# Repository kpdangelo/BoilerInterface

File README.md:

# BoilerInterface
This is an Arduino pro-mini 3.3v controlled interface between an old Tekmar controller and a new boiler.  It translates a BTU command from the controller to a Temperature setpoint for the boiler.

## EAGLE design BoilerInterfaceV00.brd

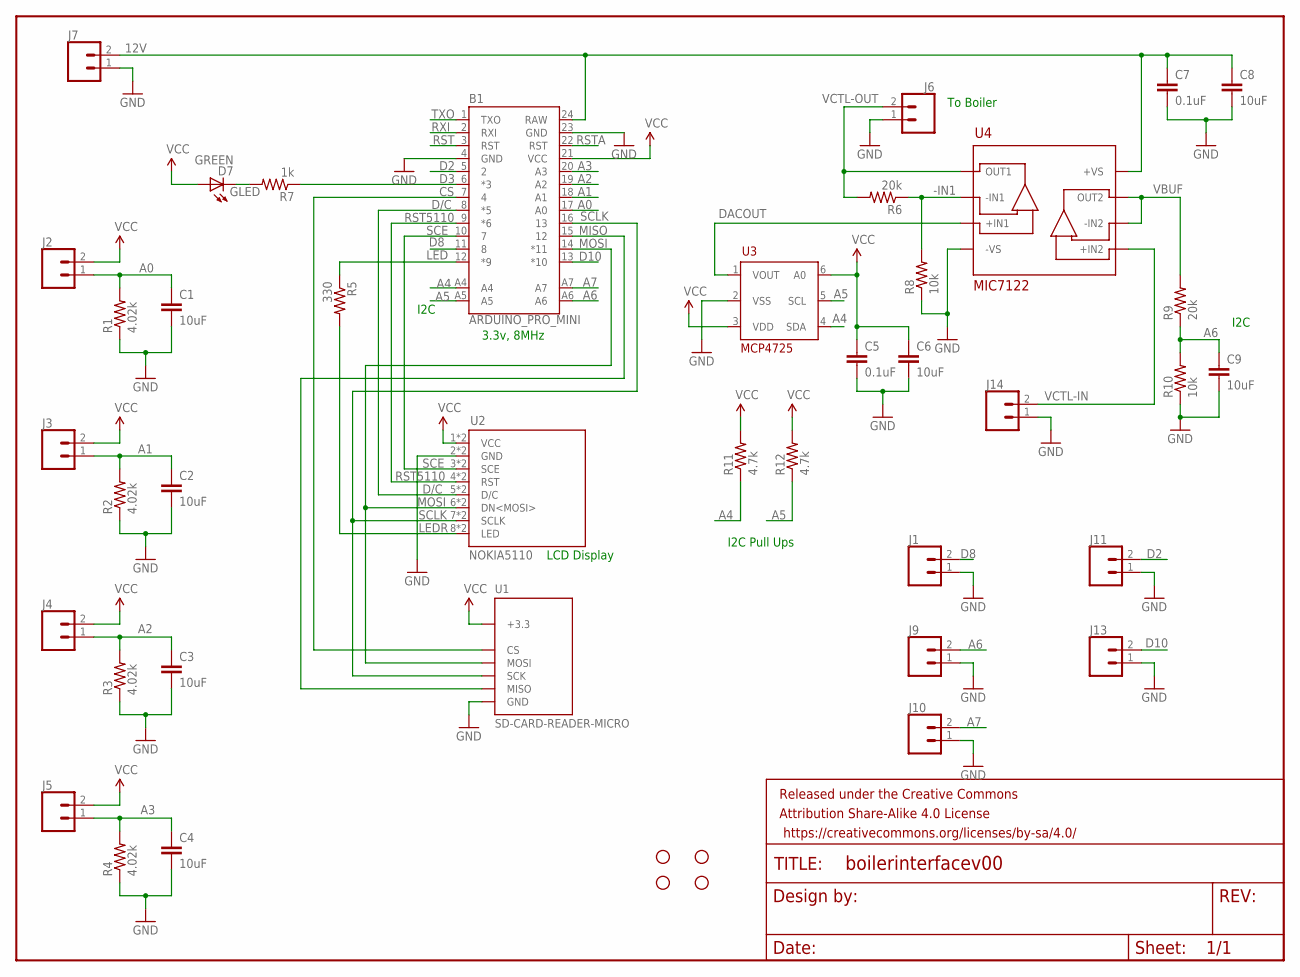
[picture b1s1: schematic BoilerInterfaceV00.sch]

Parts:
B1: ARDUINO_PRO_MINI
C1, C2, C3, C4, C6, C8, C9: 10uF; 0805
C5, C7: 0.1uF; 0805
D7: GREEN; LED-0603
FRAME1: FRAME-LETTER; CREATIVE_COMMONS
J1, J9, J10, J11, J13: CONN_02; 1X02
J2, J3, J4, J5, J6, J7, J14: CONN_025MM; SCREWTERMINAL-5MM-2
R1, R2, R3, R4: 4.02k; 0805
R5: 330; 0603-RES
R6, R9: 20k; 0805
R7: 1k; 0805
R8, R10: 10k; 0805
R11, R12: 4.7k; 0805
STANDOFF1, STANDOFF2, STANDOFF3, STANDOFF4: STAND-OFF
U1: SD-CARD-READER-MICRO; MICROSD_MOLEX
U2: NOKIA5110
U3: MCP4725; SOT23-6L
U4: MIC7122; MSOP8

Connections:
12V: B1.24 (RAW), C7.1, C8.1, J7.2, U4.8 (+VS)
-IN1: R6.1, R8.2, U4.2 (-IN1)
A0: B1.17 (A0), C1.1, J2.1, R1.2
A1: B1.18 (A1), C2.1, J3.1, R2.2
A2: B1.19 (A2), C3.1, J4.1, R3.2
A3: B1.20 (A3), C4.1, J5.1, R4.2
A4: B1.A4, R11.1, U3.4 (SDA)
A5: B1.A5, R12.1, U3.5 (SCL)
A6: B1.A6, C9.1, J9.2, R9.1, R10.2
A7: B1.A7, J10.2
CS: B1.7 (4), U1.P$2 (CS)
D2: B1.5 (2), J11.2
D3: B1.6 (*3), R7.1
D8: B1.11 (8), J1.2
D10: B1.13 (*10), J13.2
D/C: B1.8 (*5), U2.5 (D/C), U2.13 (D/C)
DACOUT: U3.1 (VOUT), U4.3 (+IN1)
GLED: D7.C, R7.2
GND: B1.4 (GND), B1.23 (GND), C1.2, C2.2, C3.2, C4.2, C5.2, C6.2, C7.2, C8.2, C9.2, J1.1, J6.1, J7.1, J9.1, J10.1, J11.1, J13.1, J14.1, R1.1, R2.1, R3.1, R4.1, R8.1, R10.1, U1.P$6 (GND), U1.P$9 (GND), U1.P$10 (GND), U1.P$11 (GND), U1.P$12 (GND), U2.2 (GND), U2.10 (GND), U3.2 (VSS), U4.4 (-VS)
LED: B1.12 (*9), R5.1
LEDR: R5.2, U2.8 (LED), U2.16 (LED)
MISO: B1.15 (12), U1.P$7 (MISO)
MOSI: B1.14 (*11), U1.P$3 (MOSI), U2.6 (DN<MOSI>), U2.14 (DN<MOSI>)
RST: B1.3 (RST)
RST5110: B1.9 (*6), U2.4 (RST), U2.12 (RST)
RSTA: B1.22 (RST)
RXI: B1.2 (RXI)
SCE: B1.10 (7), U2.3 (SCE), U2.11 (SCE)
SCLK: B1.16 (13), U1.P$5 (SCK), U2.7 (SCLK), U2.15 (SCLK)
TXO: B1.1 (TXO)
VBUF: R9.2, U4.6 (-IN2), U4.7 (OUT2)
VCC: B1.21 (VCC), C5.1, C6.1, D7.A, J2.2, J3.2, J4.2, J5.2, R11.2, R12.2, U1.P$4 (+3.3), U2.1 (VCC), U2.9 (VCC), U3.3 (VDD), U3.6 (A0)
VCTL-IN: J14.2, U4.5 (+IN2)
VCTL-OUT: J6.2, R6.2, U4.1 (OUT1)

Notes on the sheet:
To Boiler
I2C
I2C Pull Ups
3.3v, 8MHz
LCD Display

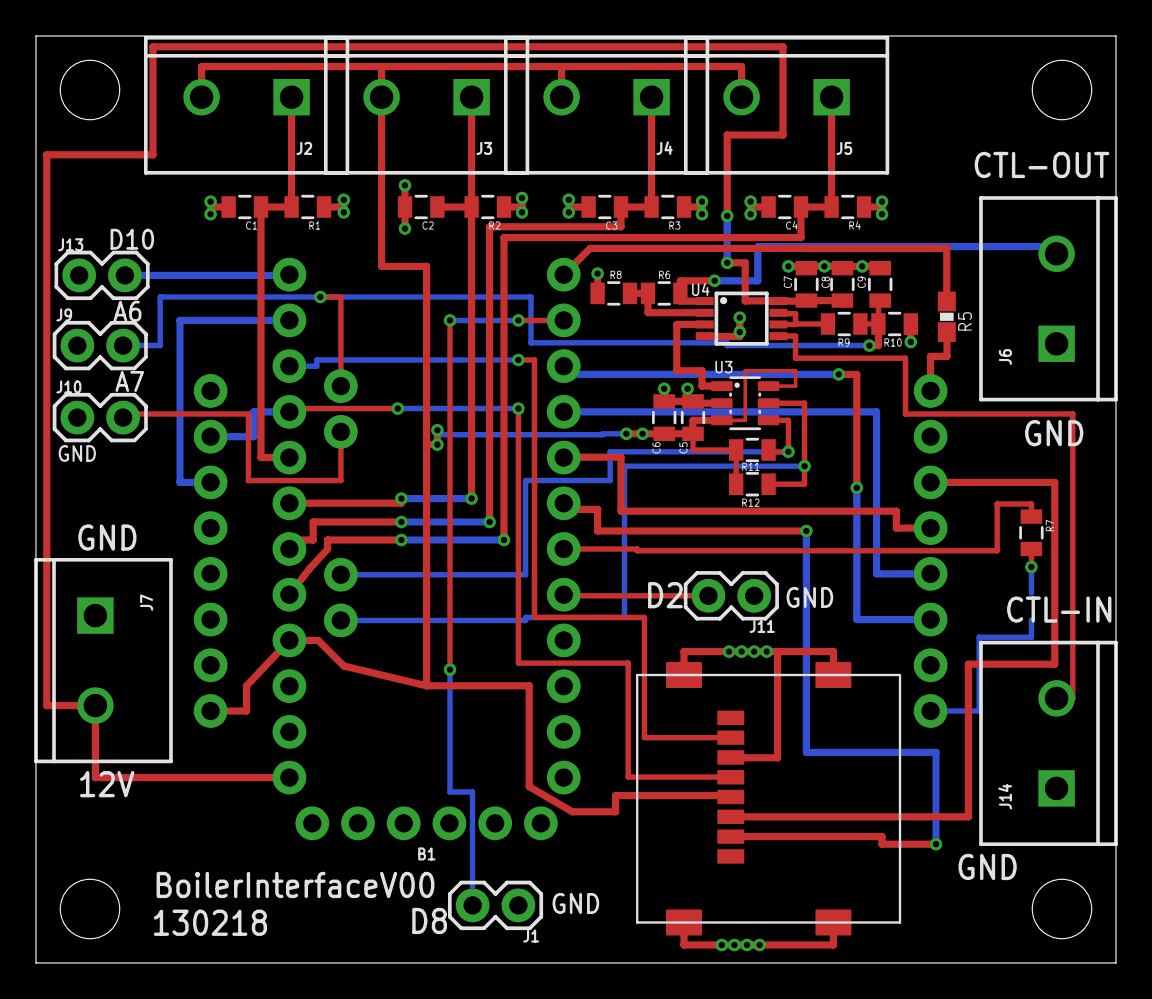
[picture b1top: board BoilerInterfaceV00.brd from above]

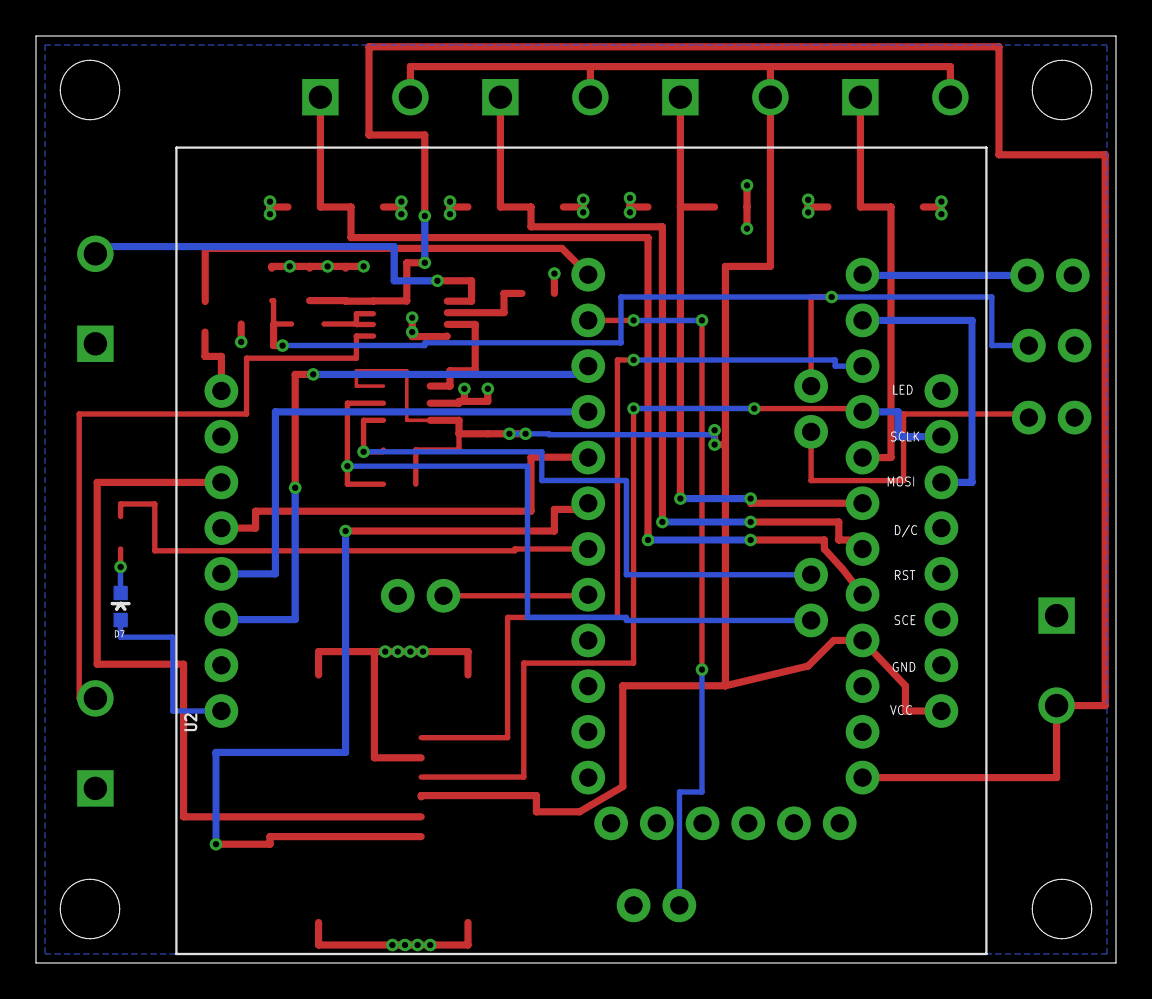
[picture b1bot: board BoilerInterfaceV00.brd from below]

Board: 2 copper layers, 60.0 x 51.5 mm, 44 parts (2 on the bottom side), 30 nets.

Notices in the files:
parts and their libraries:
SparkFun-Boards: Licensing: Creative Commons ShareAlike 4.0 International - https://creativecommons.org/licenses/by-sa/4.0
SparkFun-Aesthetics: Released under the Creative Commons
SparkFun-Aesthetics: https://creativecommons.org/licenses/by-sa/4.0
